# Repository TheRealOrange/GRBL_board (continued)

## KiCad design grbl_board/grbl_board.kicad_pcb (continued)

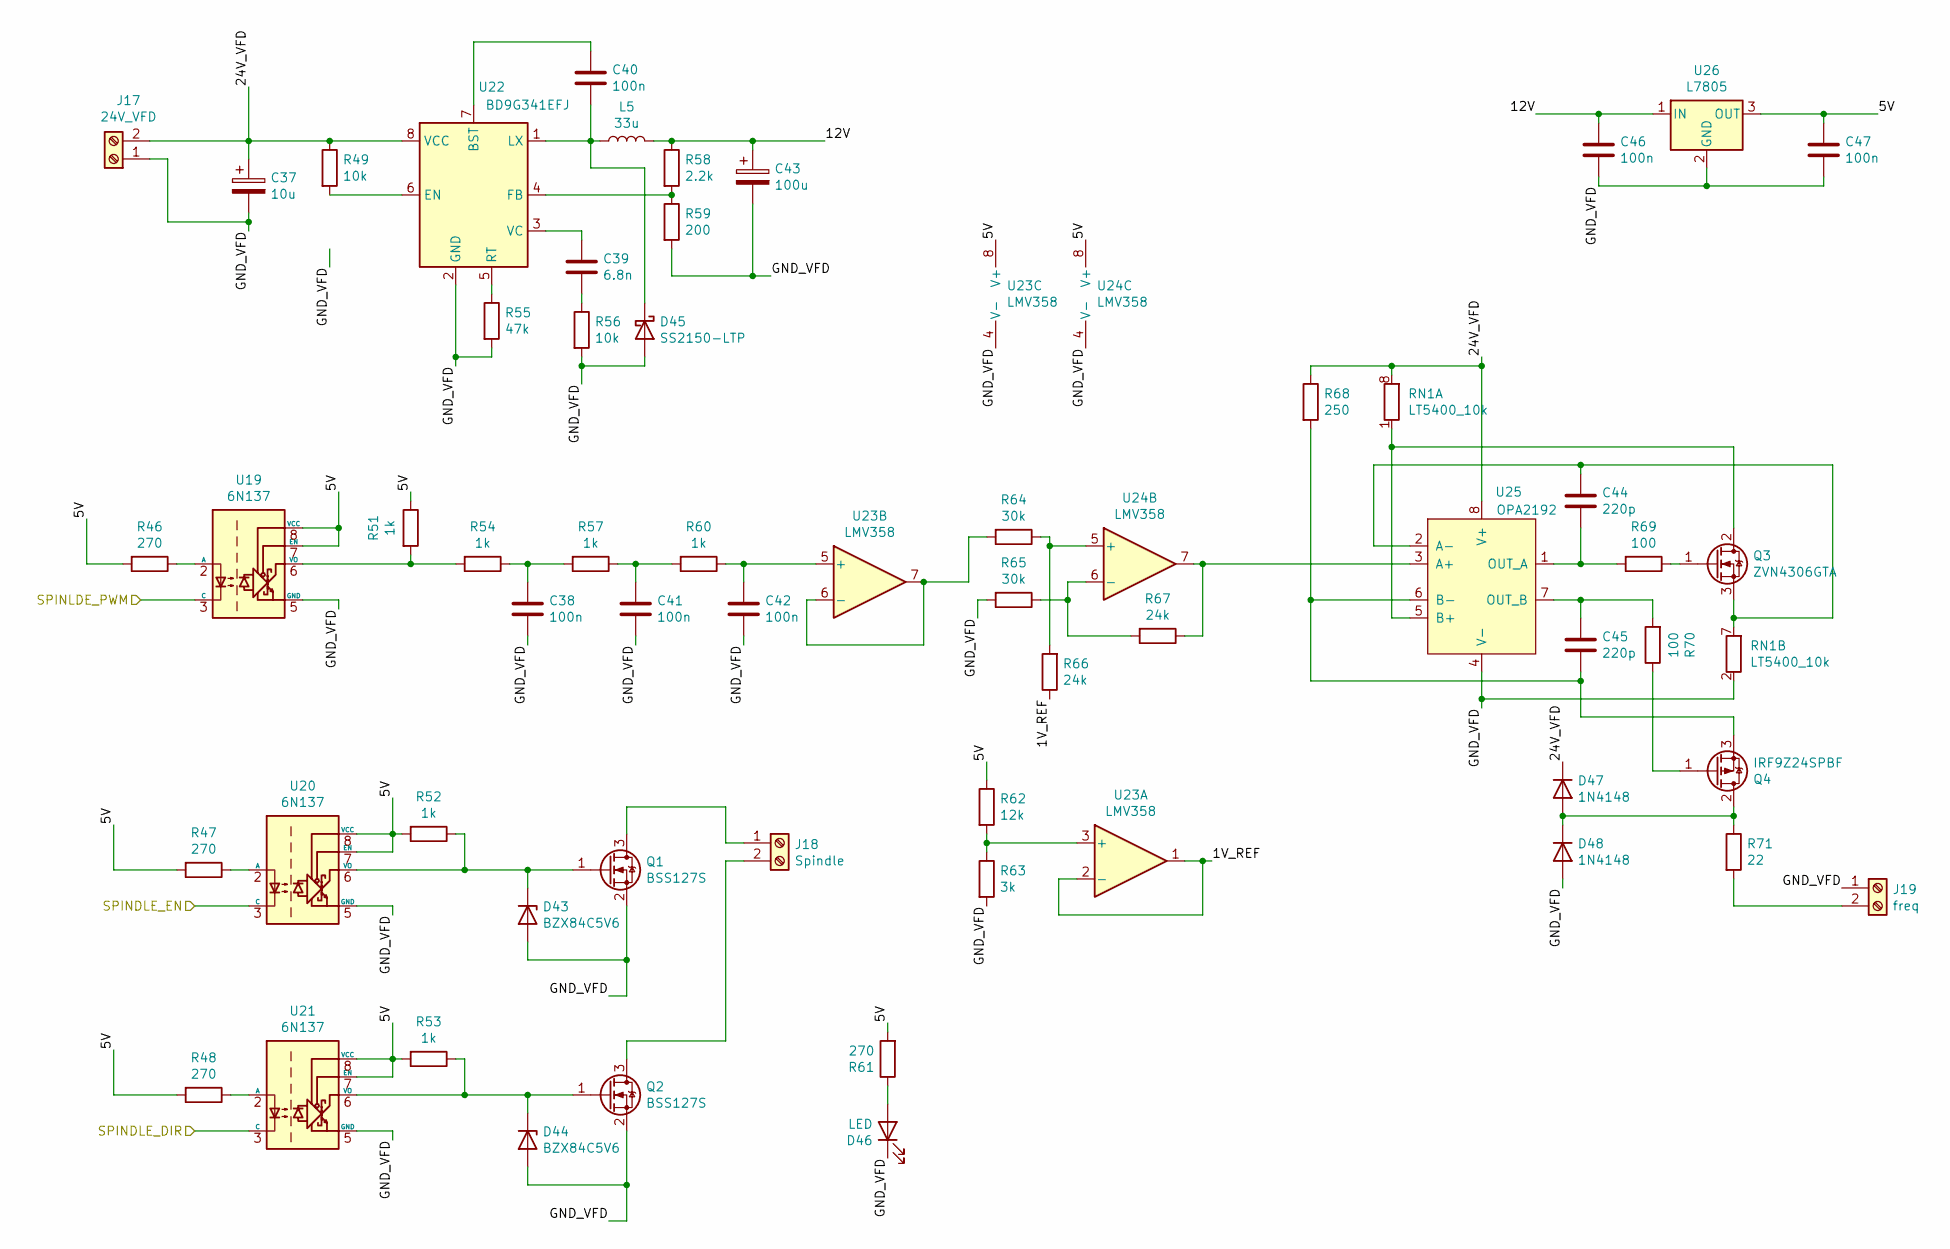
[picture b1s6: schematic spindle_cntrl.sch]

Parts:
C37: 10u; CP_Radial_D8.0mm_P3.50mm; Digikey Part No. 495-75596-ND
C38, C40, C41, C42, C46, C47: 100n; C_0603_1608Metric_Pad1.05x0.95mm_HandSolder; Digikey Part No. 1276-1941-1-ND
C39: 6.8n; C_0402_1005Metric_Pad0.74x0.62mm_HandSolder; Digikey Part No. 1276-CL05B682KB5VPNCCT-ND
C43: 100u; CP_Radial_D8.0mm_P3.50mm; Digikey Part No. 399-6119-ND
C44, C45: 220p; C_0402_1005Metric_Pad0.74x0.62mm_HandSolder; Digikey Part No. 1276-1059-1-ND
D43, D44: BZX84C5V6; D_SOT-23_ANK; Digikey Part No. 1514-BZX84C5V6TRPBFREECT-ND
D45: SS2150-LTP; D_SMA_Handsoldering; Digikey Part No. SS2150-LTPMSCT-ND
D46: LED; LED_1206_3216Metric_Pad1.42x1.75mm_HandSolder; Digikey Part No. 404-1046-1-ND
D47, D48: 1N4148; D_DO-35_SOD27_P7.62mm_Horizontal; Digikey Part No. 1N4148FS-ND
J17: 24V_VFD; PhoenixContact_MC_1,5_2-G-3.81_1x02_P3.81mm_Horizontal; Digikey Part No. ED2808-ND
J18: Spindle; PhoenixContact_MC_1,5_2-G-3.81_1x02_P3.81mm_Horizontal; Digikey Part No. ED2808-ND
J19: freq; PhoenixContact_MC_1,5_2-G-3.81_1x02_P3.81mm_Horizontal; Digikey Part No. ED2808-ND
L5: 33u; L_Vishay_IHLP-4040; Digikey Part No. 541-2273-1-ND
Q1, Q2: BSS127S; SOT-23; Digikey Part No. BSS127S-7DICT-ND
Q3: ZVN4306GTA; SOT-223-3_TabPin2; Digikey Part No. ZVN4306GCT-ND
Q4: IRF9Z24SPBF; TO-263-3_TabPin2; Digikey Part No. IRF9Z24SPBF-ND
R46, R47, R48, R61: 270; R_0805_2012Metric_Pad1.15x1.40mm_HandSolder; Digikey Part No. YAG6172CT-ND
R49, R56: 10k; R_0805_2012Metric_Pad1.15x1.40mm_HandSolder; Digikey Part No. 311-10KARCT-ND
R51, R52, R53, R54, R57, R60: 1k; R_0805_2012Metric_Pad1.15x1.40mm_HandSolder; Digikey Part No. 311-10KARCT-ND
R55: 47k; R_0805_2012Metric_Pad1.15x1.40mm_HandSolder; Digikey Part No. 311-47KARCT-ND
R58: 2.2k; R_0603_1608Metric_Pad0.98x0.95mm_HandSolder; Digikey Part No. 311-2.2KGRCT-ND
R59: 200; R_0603_1608Metric_Pad0.98x0.95mm_HandSolder; Digikey Part No. 311-200GRCT-ND
R62: 12k; R_0805_2012Metric_Pad1.15x1.40mm_HandSolder; Digikey Part No. 311-12KARCT-ND
R63: 3k; R_0603_1608Metric_Pad0.98x0.95mm_HandSolder; Digikey Part No. 311-3.0KGRCT-ND
R64, R65: 30k; R_0603_1608Metric_Pad0.98x0.95mm_HandSolder; Digikey Part No. 311-30KGRCT-ND
R66, R67: 24k; R_0805_2012Metric_Pad1.15x1.40mm_HandSolder; Digikey Part No. 311-24KARCT-ND
R68: 250; R_0603_1608Metric_Pad0.98x0.95mm_HandSolder; Digikey Part No. 13-RT0603BRE07250RLCT-ND
R69, R70: 100; R_0603_1608Metric_Pad0.98x0.95mm_HandSolder; Digikey Part No. 311-100GRCT-ND
R71: 22; R_0805_2012Metric_Pad1.15x1.40mm_HandSolder; Digikey Part No. 13-RT0805BRD0722RLCT-ND
RN1: LT5400_10k; TSSOP-8_3x3mm_P0.65mm; Digikey Part No. 505-LT5400ACMS8E-1#PBF-ND
U19, U20, U21: 6N137; DIP-8_W7.62mm_Socket; Digikey Part No. 6N137IS-ND
U22: BD9G341EFJ; HTSOP-8-1EP_3.9x4.9mm_P1.27mm_EP2.4x3.2mm_ThermalVias; Digikey Part No. BD9G341AEFJ-E2CT-ND
U23, U24: LMV358; SOIC-8_3.9x4.9mm_P1.27mm; Digikey Part No. LMV358DR2GOSCT-ND
U25: OPA2192; TSSOP-8_3x3mm_P0.65mm; Digikey Part No. 296-50480-1-ND
U26: L7805; TO-263-2; Digikey Part No. 497-1170-1-ND

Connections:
/grbl_controller/SPINDLE_DIR: U21.3 (C); also elsewhere on the board
/grbl_controller/SPINDLE_EN: U20.3 (C); also elsewhere on the board
/grbl_controller/SPINDLE_PWM: U19.3 (C); also elsewhere on the board
/spindle_cntrl/1V_REF: R66.1, U23.1, U23.2 (-)
/spindle_cntrl/5V: C47.1, R46.2, R47.2, R48.2, R51.1, R52.2, R53.2, R61.2, R62.1, U19.7 (EN), U19.8 (VCC), U20.7 (EN), U20.8 (VCC), U21.7 (EN), U21.8 (VCC), U23.8 (V+), U24.8 (V+), U26.3 (OUT)
/spindle_cntrl/12V: C43.1, C46.1, L5.2, R58.1, U26.1 (IN)
/spindle_cntrl/24V_VFD: C37.1, D47.1 (K), J17.2, R49.1, R68.1, RN1.8 (R1.2), U22.8 (VCC), U25.8 (V+)
/spindle_cntrl/GND_VFD: C37.2, C38.2, C41.2, C42.2, C43.2, C46.2, C47.2, D43.2 (A), D44.2 (A), D45.2 (A), D46.1 (K), D48.2 (A), J17.1, J19.1, Q1.2 (S), Q2.2 (S), R55.2, R56.2, R59.2, R63.2, R65.2, RN1.2 (R2.1), U19.5 (GND), U20.5 (GND), U21.5 (GND), U22.2 (GND), U23.4 (V-), U24.4 (V-), U25.4 (V-), U26.2 (GND)
unnamed: C38.1, R54.1, R57.2
unnamed: C39.1, U22.3 (VC)
unnamed: C39.2, R56.1
unnamed: C40.1, U22.7 (BST)
unnamed: C40.2, D45.1 (K), L5.1, U22.1 (LX)
unnamed: C41.1, R57.1, R60.2
unnamed: C42.1, R60.1, U23.5 (+)
unnamed: C44.1, Q3.3 (S), RN1.7 (R2.2), U25.2 (A-)
unnamed: C44.2, R69.2, U25.1 (OUT_A)
unnamed: C45.1, R70.2, U25.7 (OUT_B)
unnamed: C45.2, Q4.3 (S), R68.2, U25.6 (B-)
unnamed: D43.1 (K), Q1.1 (G), R52.1, U20.6 (VO)
unnamed: D44.1 (K), Q2.1 (G), R53.1, U21.6 (VO)
unnamed: D46.2 (A), R61.1
unnamed: D47.2 (A), D48.1 (K), Q4.2 (D), R71.1
unnamed: J18.1, Q1.3 (D)
unnamed: J18.2, Q2.3 (D)
unnamed: J19.2, R71.2
unnamed: Q3.1 (G), R69.1
unnamed: Q3.2 (D), RN1.1 (R1.1), U25.5 (B+)
unnamed: Q4.1 (G), R70.1
unnamed: R46.1, U19.2 (A)
unnamed: R47.1, U20.2 (A)
unnamed: R48.1, U21.2 (A)
unnamed: R49.2, U22.6 (EN)
unnamed: R51.2, R54.2, U19.6 (VO)
unnamed: R55.1, U22.5 (RT)
unnamed: R58.2, R59.1, U22.4 (FB)
unnamed: R62.2, R63.1, U23.3 (+)
unnamed: R64.1, R66.2, U24.5 (+)
unnamed: R64.2, U23.6 (-), U23.7
unnamed: R65.1, R67.2, U24.6 (-)
unnamed: R67.1, U24.7, U25.3 (A+)

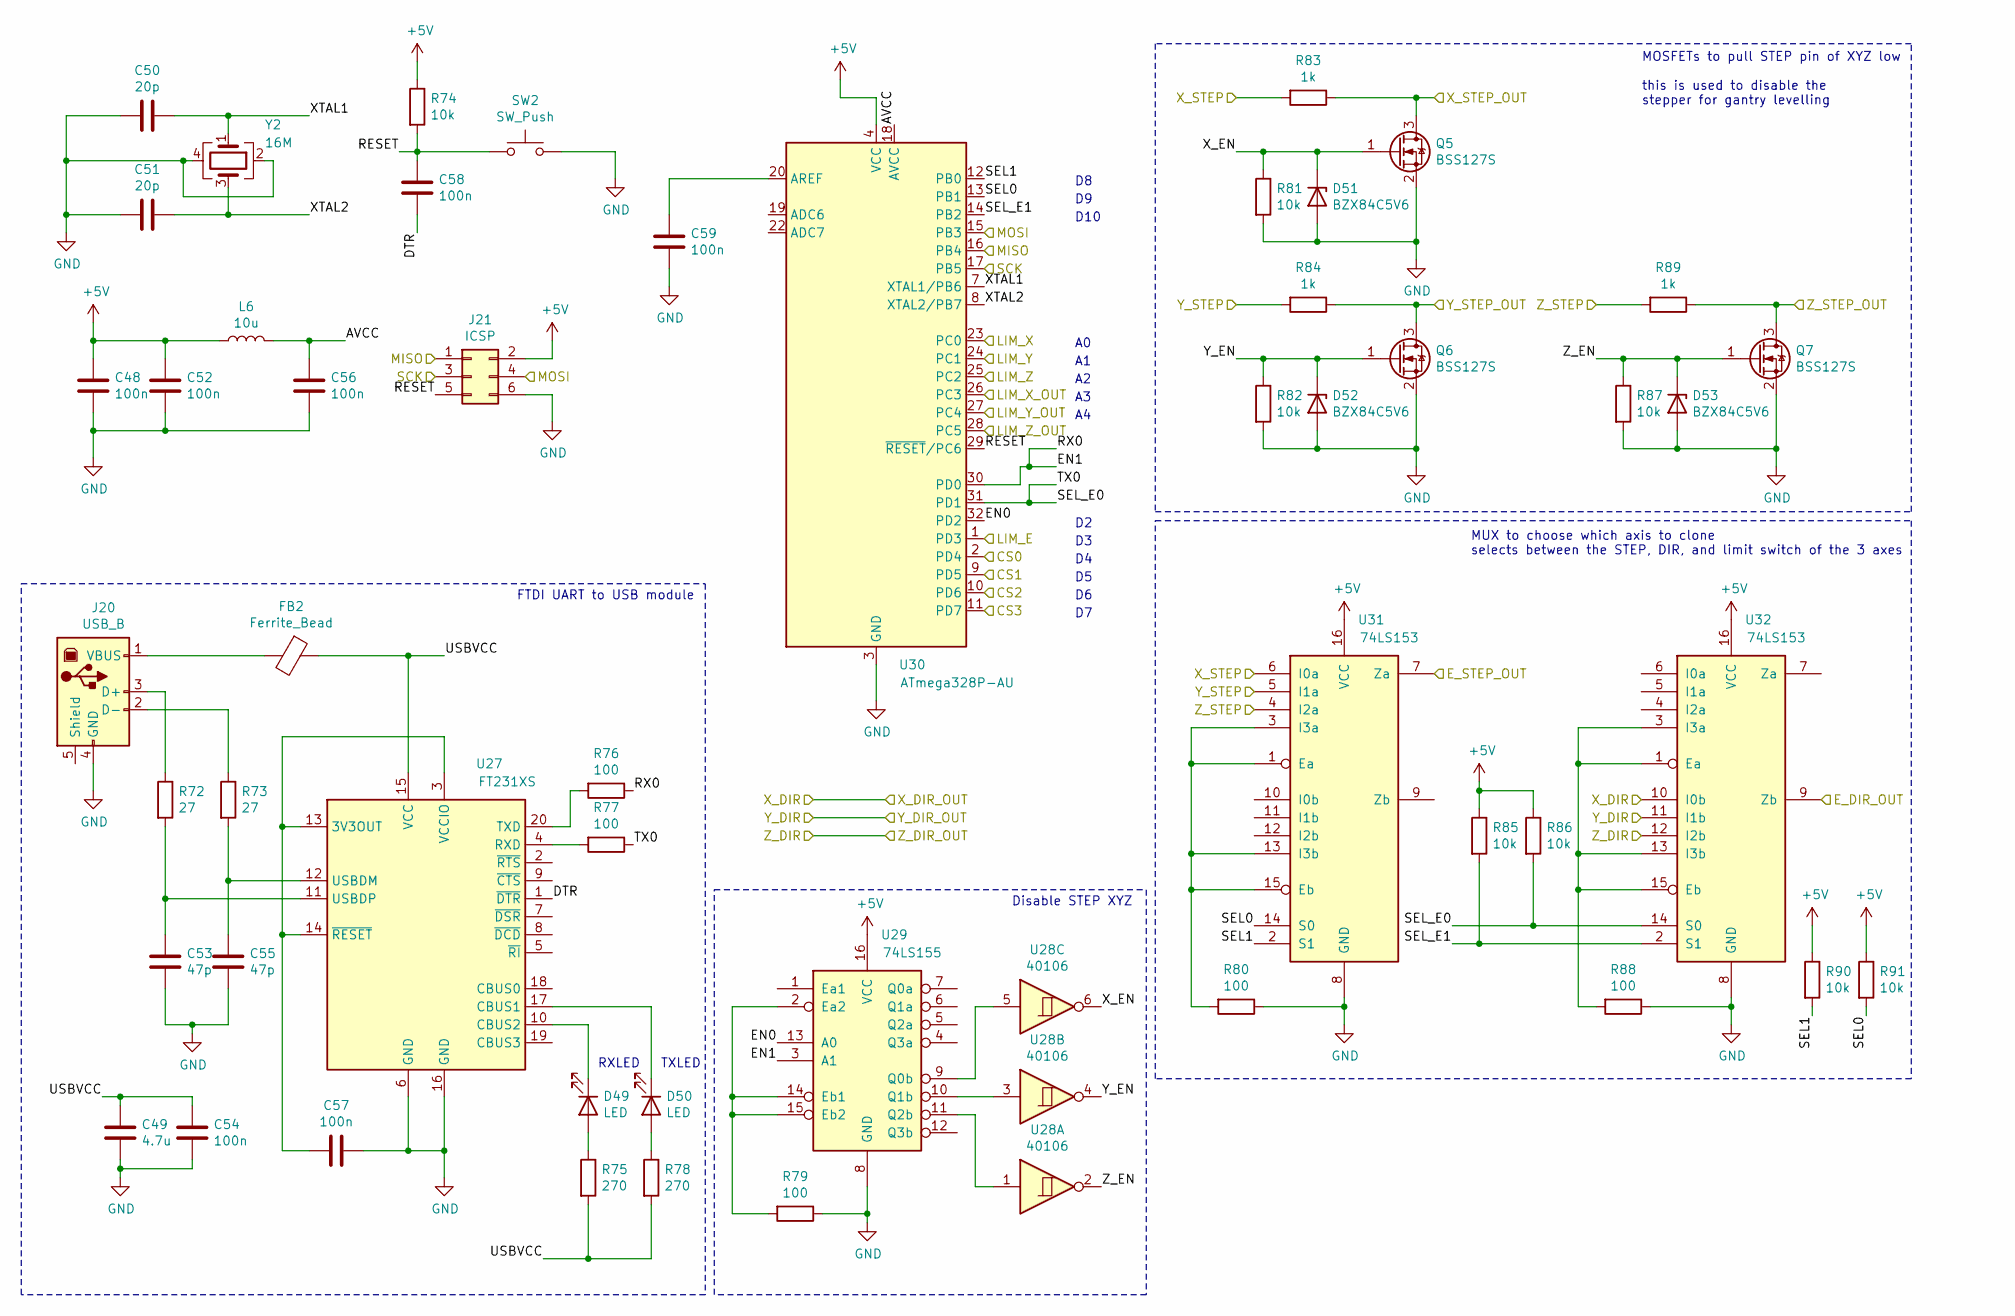
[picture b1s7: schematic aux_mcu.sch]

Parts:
C48, C52, C54, C56, C57, C58, C59: 100n; C_0603_1608Metric_Pad1.05x0.95mm_HandSolder; Digikey Part No. 1276-1941-1-ND
C49: 4.7u; C_1206_3216Metric_Pad1.33x1.80mm_HandSolder; Digikey Part No. 1276-6781-1-ND
C50, C51: 20p; C_0603_1608Metric_Pad1.05x0.95mm_HandSolder; Digikey Part No. 1276-1187-1-ND
C53, C55: 47p; C_0402_1005Metric_Pad0.74x0.62mm_HandSolder; Digikey Part No. 1276-1699-1-ND
D49, D50: LED; LED_1206_3216Metric_Pad1.42x1.75mm_HandSolder; Digikey Part No. 404-1042-1-ND
D51, D52, D53: BZX84C5V6; D_SOT-23_ANK; Digikey Part No. 1514-BZX84C5V6TRPBFREECT-ND
FB2: Ferrite_Bead; C_0603_1608Metric_Pad1.05x0.95mm_HandSolder; Digikey Part No. 732-1591-1-ND
J20: USB_B; USB_B_OST_USB-B1HSxx_Horizontal; Digikey Part No. 380-1492-ND
J21: ICSP; PinHeader_2x03_P2.54mm_Vertical; Digikey Part No. 609-3234-ND
L6: 10u; L_0805_2012Metric_Pad1.05x1.20mm_HandSolder; Digikey Part No. 490-4029-1-ND
Q5, Q6, Q7: BSS127S; SOT-23; Digikey Part No. BSS127S-7DICT-ND
R72, R73: 27; R_0603_1608Metric_Pad0.98x0.95mm_HandSolder; Digikey Part No. 311-27GRCT-ND
R74, R81, R82, R85, R86, R87, R90, R91: 10k; R_0805_2012Metric_Pad1.15x1.40mm_HandSolder; Digikey Part No. 311-10KARCT-ND
R75, R78: 270; R_0805_2012Metric_Pad1.15x1.40mm_HandSolder; Digikey Part No. YAG6172CT-ND
R76, R77, R79, R80, R88: 100; R_0603_1608Metric_Pad0.98x0.95mm_HandSolder; Digikey Part No. 311-100GRCT-ND
R83, R84, R89: 1k; R_1206_3216Metric_Pad1.30x1.75mm_HandSolder; Digikey Part No. 311-1.0KERCT-ND
SW2: SW_Push; SW_Push_1P1T_NO_6x6mm_H9.5mm; Digikey Part No. EG2526CT-ND
U27: FT231XS; SSOP-20_3.9x8.7mm_P0.635mm; Digikey Part No. 768-1129-1-ND
U28: 40106; TSSOP-14_4.4x5mm_P0.65mm; Digikey Part No. HEF40106BTT,112-ND
U29: 74LS155; SOIC-16_3.9x9.9mm_P1.27mm; Digikey Part No. 296-33960-5-ND
U30: ATmega328P-AU; TQFP-32_7x7mm_P0.8mm; Digikey Part No. ATMEGA328P-AU-ND
U31, U32: 74LS153; SOIC-16_3.9x9.9mm_P1.27mm; Digikey Part No. 296-3653-5-ND
Y2: 16M; Crystal_SMD_SeikoEpson_TSX3225-4Pin_3.2x2.5mm_HandSoldering; Digikey Part No. SER4372CT-ND

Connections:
+5V: C48.1, C52.1, J21.2, L6.1, R74.1, R85.1, R86.1, R90.1, R91.1, U29.16 (VCC), U30.4 (VCC), U30.6 (VCC), U31.16 (VCC), U32.16 (VCC); also elsewhere on the board
/CS_E: U30.11 (PD7); also elsewhere on the board
/CS_X: U30.2 (PD4); also elsewhere on the board
/CS_Y: U30.9 (PD5); also elsewhere on the board
/CS_Z: U30.10 (PD6); also elsewhere on the board
/MISO: J21.1, U30.16 (PB4); also elsewhere on the board
/MOSI: J21.4, U30.15 (PB3); also elsewhere on the board
/SCK: J21.3, U30.17 (PB5); also elsewhere on the board
/aux_mcu/AVCC: C56.1, L6.2, U30.18 (AVCC)
/aux_mcu/DTR: C58.2, U27.1 (~DTR)
/aux_mcu/EN0: U29.13 (A0), U30.32 (PD2)
/aux_mcu/EN1: R76.1, U29.3 (A1), U30.30 (PD0)
/aux_mcu/LIM_E: U30.1 (PD3); also elsewhere on the board
/aux_mcu/LIM_X: U30.23 (PC0); also elsewhere on the board
/aux_mcu/LIM_Y: U30.24 (PC1); also elsewhere on the board
/aux_mcu/LIM_Z: U30.25 (PC2); also elsewhere on the board
/aux_mcu/RESET: C58.1, J21.5, R74.2, SW2.1, U30.29 (~RESET~/PC6)
/aux_mcu/SEL0: R91.2, U30.13 (PB1), U31.14 (S0)
/aux_mcu/SEL1: R90.2, U30.12 (PB0), U31.2 (S1)
/aux_mcu/SEL_E0: R77.1, R86.2, U30.31 (PD1), U32.14 (S0)
/aux_mcu/SEL_E1: R85.2, U30.14 (PB2), U32.2 (S1)
/aux_mcu/USBVCC: C49.1, C54.1, FB2.1, R75.2, R78.2, U27.15 (VCC)
/aux_mcu/XTAL1: C50.1, U30.7 (XTAL1/PB6), Y2.1
/aux_mcu/XTAL2: C51.1, U30.8 (XTAL2/PB7), Y2.3
/aux_mcu/X_EN: D51.1 (K), Q5.1 (G), R81.1, U28.6
/aux_mcu/Y_EN: D52.1 (K), Q6.1 (G), R82.1, U28.4
/aux_mcu/Z_EN: D53.1 (K), Q7.1 (G), R87.1, U28.2
/grbl_controller/DIR_X: U32.10 (I0b); also elsewhere on the board
/grbl_controller/DIR_Y: U32.11 (I1b); also elsewhere on the board
/grbl_controller/DIR_Z: U32.12 (I2b); also elsewhere on the board
/grbl_controller/LIM_X: U30.26 (PC3); also elsewhere on the board
/grbl_controller/LIM_Y: U30.27 (PC4); also elsewhere on the board
/grbl_controller/LIM_Z: U30.28 (PC5); also elsewhere on the board
/grbl_controller/STEP_X: R83.2, U31.6 (I0a); also elsewhere on the board
/grbl_controller/STEP_Y: R84.2, U31.5 (I1a); also elsewhere on the board
/grbl_controller/STEP_Z: R89.2, U31.4 (I2a); also elsewhere on the board
/stepper_drivers/E_DIR: U32.9 (Zb); also elsewhere on the board
/stepper_drivers/E_STEP: U31.7 (Za); also elsewhere on the board
/stepper_drivers/X_STEP: Q5.3 (D), R83.1; also elsewhere on the board
/stepper_drivers/Y_STEP: Q6.3 (D), R84.1; also elsewhere on the board
/stepper_drivers/Z_STEP: Q7.3 (D), R89.1; also elsewhere on the board
GND: C48.2, C49.2, C50.2, C51.2, C52.2, C53.2, C54.2, C55.2, C56.2, C57.1, C59.2, D51.2 (A), D52.2 (A), D53.2 (A), J20.4 (GND), J21.6, Q5.2 (S), Q6.2 (S), Q7.2 (S), R79.1, R80.1, R81.2, R82.2, R87.2, R88.1, SW2.2, U27.6 (GND), U27.16 (GND), U29.8 (GND), U30.3 (GND), U30.5 (GND), U30.21 (GND), U31.8 (GND), U32.8 (GND), Y2.2, Y2.4; also elsewhere on the board
unnamed: C53.1, R72.2, U27.11 (USBDP)
unnamed: C55.1, R73.2, U27.12 (USBDM)
unnamed: C57.2, U27.3 (VCCIO), U27.13 (3V3OUT), U27.14 (~RESET)
unnamed: C59.1, U30.20 (AREF)
unnamed: D49.1 (K), U27.10 (CBUS2)
unnamed: D49.2 (A), R75.1
unnamed: D50.1 (K), U27.17 (CBUS1)
unnamed: D50.2 (A), R78.1
unnamed: FB2.2, J20.1 (VBUS)
unnamed: J20.2 (D-), R73.1
unnamed: J20.3 (D+), R72.1
unnamed: R76.2, U27.20 (TXD)
unnamed: R77.2, U27.4 (RXD)
unnamed: R79.2, U29.2 (Ea2), U29.14 (Eb1), U29.15 (Eb2)
unnamed: R80.2, U31.1 (Ea), U31.3 (I3a), U31.13 (I3b), U31.15 (Eb)
unnamed: R88.2, U32.1 (Ea), U32.3 (I3a), U32.13 (I3b), U32.15 (Eb)
unnamed: U28.1, U29.11 (Q2b)
unnamed: U28.3, U29.10 (Q1b)
unnamed: U28.5, U29.9 (Q0b)

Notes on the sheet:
D10
TXLED
RXLED
FTDI UART to USB module
Disable STEP XYZ
MOSFETs to pull STEP pin of XYZ low this is used to disable the stepper for gantry levelling
MUX to choose which axis to clone selects between the STEP, DIR, and limit switch of the 3 axes

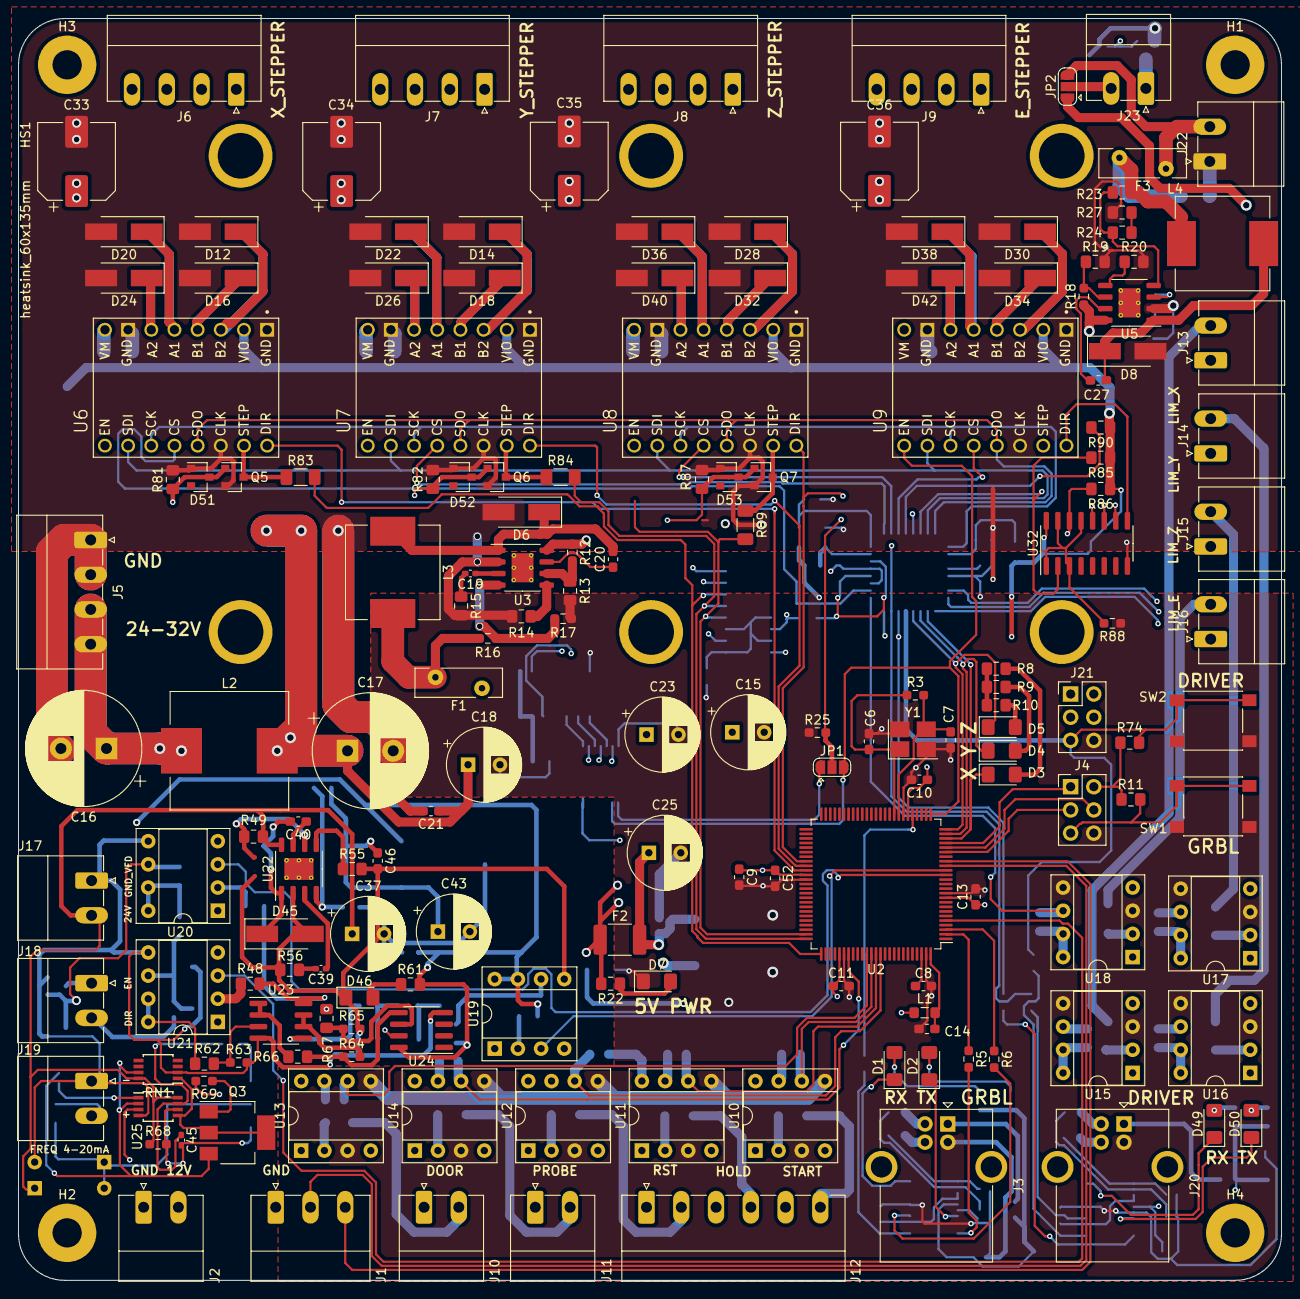
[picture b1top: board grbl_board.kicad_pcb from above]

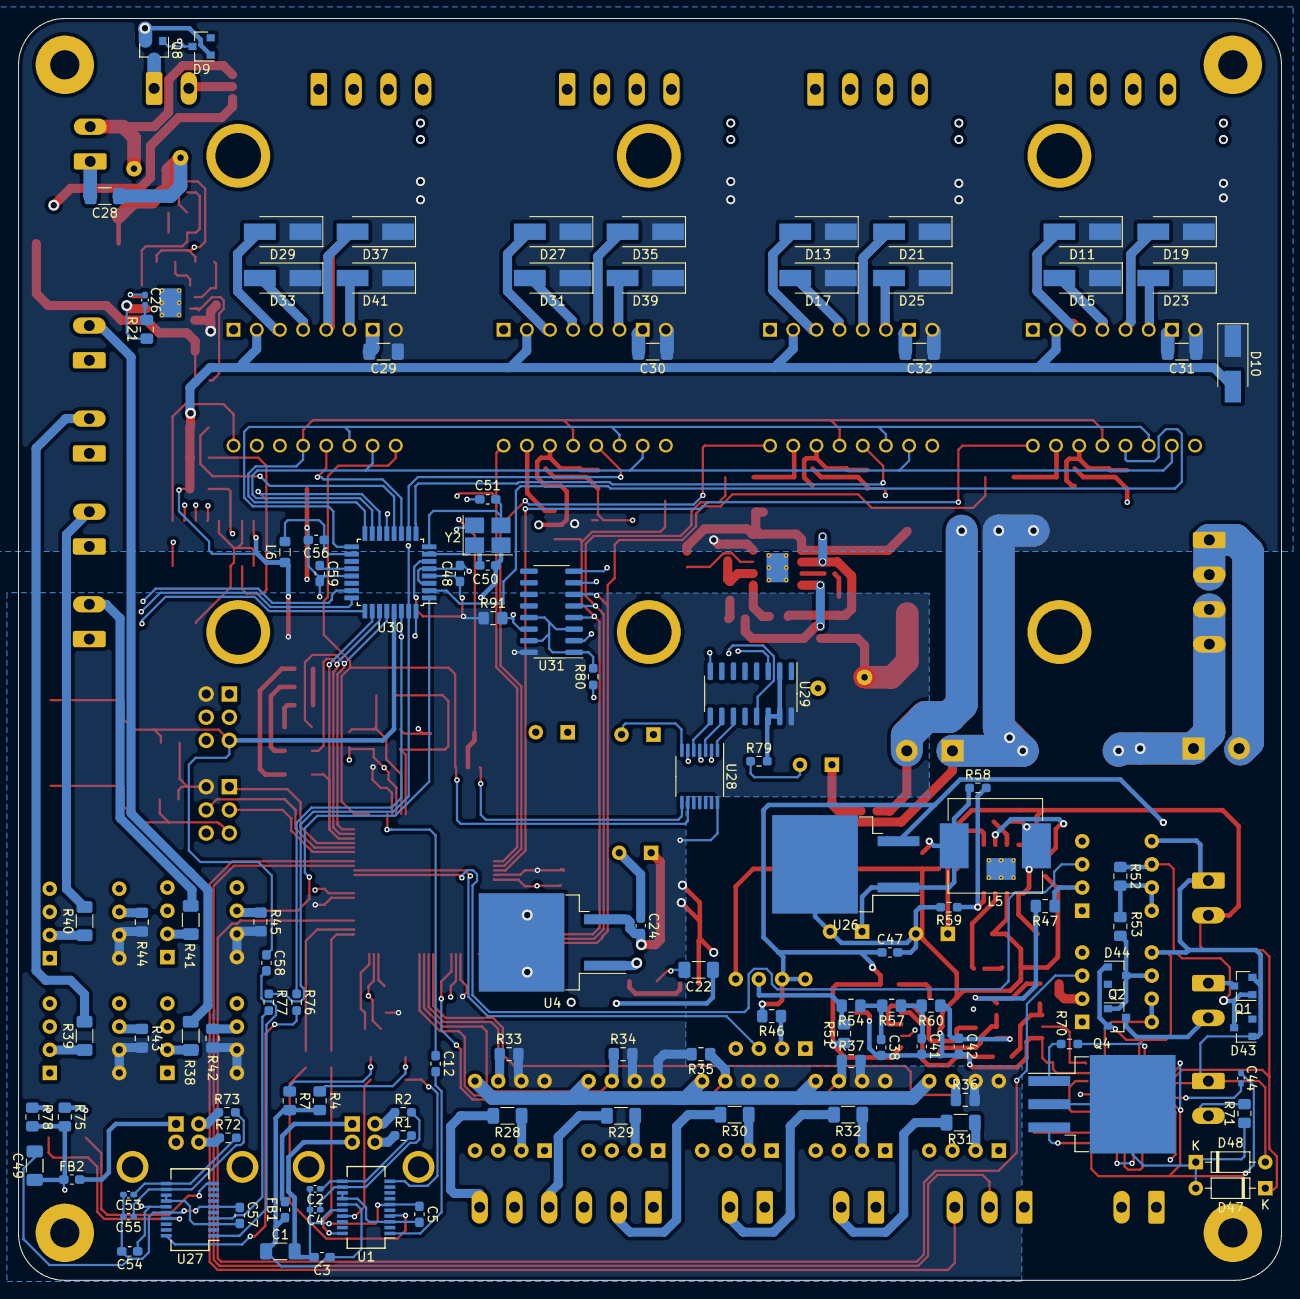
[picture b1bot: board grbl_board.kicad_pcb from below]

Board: 4 copper layers, 138.4 x 138.3 mm, 287 parts (113 on the bottom side), 199 nets.

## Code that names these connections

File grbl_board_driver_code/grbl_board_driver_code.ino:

#include <TMCStepper.h>

//#define TMCSTEPPER

#define CLONED_AXIS           1  //0:x, 1:y, 2:z
#define LIMIT_INVERT       false

// stepper motor config
#define MICROSTEPS            0
#define CURRENT_MA         2500
#define HOLD_MULTIPLIER     0.8
#define INTERPOLATE        true

#define STEALTHCHOP       false

// experimental
//#define SQUARE_WAVE_STEPPING

#define CHOPPER_TIMING {4, -2, 1}

#define LIM_X_IN     A0
#define LIM_Y_IN     A1
#define LIM_Z_IN     A2

#define LIM_X_OUT    A3
#define LIM_Y_OUT    A4
#define LIM_Z_OUT    A5

#define LIM_E        3

#define EN0 2
#define EN1 0

#define SEL0 9
#define SEL1 8

#define SEL_E0 1
#define SEL_E1 10

#define CS_X 4
#define CS_Y 5
#define CS_Z 6
#define CS_E 7

uint8_t lim_e_val = 0, lim_cloned_val = 0;
boolean pulloff = false;
long levelling = -1;

#define R_SENSE 0.075f // Match to your driver
                      // SilentStepStick series use 0.11
                      // UltiMachine Einsy and Archim2 boards use 0.2
                      // Panucatt BSD2660 uses 0.1
                      // Watterott TMC5160 uses 0.075

typedef struct {
  uint8_t toff;    // [1..15]
  int8_t hend;     // [-3..12]
  uint8_t hstrt;   // [1..8]
} chopper_timing_t;

#ifdef TMCSTEPPER
  TMC5160Stepper x_stepper(CS_X, R_SENSE);
  TMC5160Stepper y_stepper(CS_Y, R_SENSE);
  TMC5160Stepper z_stepper(CS_Z, R_SENSE);
  TMC5160Stepper e_stepper(CS_E, R_SENSE);
  
  TMC5160Stepper steppers[] = {x_stepper, y_stepper, z_stepper, e_stepper};
  int8_t timings[] = CHOPPER_TIMING; // Default 4, -2, 1
  static constexpr chopper_timing_t chop_init = CHOPPER_TIMING;
#endif
int8_t enable = LOW , disable = HIGH;


void stopStepper(int num) {
  digitalWrite(EN0, num&0x1);
  digitalWrite(EN1, (num&0x2) >> 1);
}

void selectStepClone(int num) {
  digitalWrite(SEL0, num&0x1);
  digitalWrite(SEL1, (num&0x2) >> 1);
}

void selectAxisClone(int num) {
  digitalWrite(SEL_E0, num&0x1);
  digitalWrite(SEL_E1, (num&0x2) >> 1);
}

void setup() {
  pinMode(SEL0, OUTPUT);
  pinMode(SEL1, OUTPUT);
  pinMode(SEL_E0, OUTPUT);
  pinMode(SEL_E1, OUTPUT);
  pinMode(EN0, OUTPUT);
  pinMode(EN1, OUTPUT);
  
  pinMode(LIM_X_OUT, OUTPUT);
  pinMode(LIM_Y_OUT, OUTPUT);
  pinMode(LIM_Z_OUT, OUTPUT);

  pinMode(LIM_X_IN, INPUT_PULLUP);
  pinMode(LIM_Y_IN, INPUT_PULLUP);
  pinMode(LIM_Z_IN, INPUT_PULLUP);

  pinMode(LIM_E, INPUT_PULLUP);

  pinMode(CS_X, OUTPUT);
  pinMode(CS_Y, OUTPUT);
  pinMode(CS_Z, OUTPUT);
  pinMode(CS_E, OUTPUT);

  if (LIMIT_INVERT) {
    enable = HIGH;
    disable = LOW;
  }

  #ifdef TMCSTEPPER
    SPI.begin();
    
    for (auto& st: steppers){
      st.begin();                 //  SPI: Init CS pins and possible SW SPI pins
      st.reset();
      st.toff(0);
      st.push();
      st.toff(chop_init.toff);
      
      CHOPCONF_t chopconf{0};
      chopconf.tbl = 0b01;
      chopconf.toff = chop_init.toff;
      chopconf.intpol = INTERPOLATE;
      chopconf.hend = chop_init.hend + 3;
      chopconf.hstrt = chop_init.hstrt - 1;
      #ifdef SQUARE_WAVE_STEPPING
        chopconf.dedge = true;
      #endif
      st.CHOPCONF(chopconf.sr);
      
      st.rms_current(CURRENT_MA, HOLD_MULTIPLIER);
      st.microsteps(MICROSTEPS);
      st.iholddelay(10);
      st.TPOWERDOWN(128); // ~2s until driver lowers to hold current
      
      st.en_pwm_mode(STEALTHCHOP); // Toggle stealthChop on TMC2130/2160/5130/5160
      st.TPWMTHRS(500);   
      st.TCOOLTHRS(0xFFFFF); // 20bit max - Lower velocity threshold for switching on CoolStep and stop on stall. Below this velocity CoolStep becomes disabled (not used in STEP/DIR mode). Adapt to the lower limit of the velocity range where StallGuard2 gives a stable result.
      st.THIGH(0);    // Upper velocity threshold value for CoolStep and stop on stall. Above this velocity CoolStep becomes disabled. Adapt to the velocity range where StallGuard2 gives a stable result.
      st.semin(5);    // [0-15] If the StallGuard2 result falls below SEMIN*32, the motor current becomes increased to reduce motor load angle. 0 = smart current control CoolStep off
      st.semax(2);    // [0-15] If the StallGuard2 result is equal to or above (SEMIN+SEMAX+1)*32, the motor current becomes decreased to save energy.
      st.sedn(0b01);  // For each 8 StallGuard2 values decrease by one
     
      TMC2160_n::PWMCONF_t pwmconf{0};
      pwmconf.pwm_lim = 12;
      pwmconf.pwm_reg = 8;
      pwmconf.pwm_autograd = true;
      pwmconf.pwm_autoscale = true;
      pwmconf.pwm_freq = 0b01;
      pwmconf.pwm_grad = 14;
      pwmconf.pwm_ofs = 36;
      st.PWMCONF(pwmconf.sr);
      st.drvstrength(0b11);   // 00: weak  01: weak+TC (medium above OTPW level)  10: medium  11: strong  
  
      st.sfilt(true);
      
      st.GSTAT(); // Clear GSTAT
      st.RAMP_STAT();
  
    }
  #else
    pinMode(11, OUTPUT);
    pinMode(12, OUTPUT);
    pinMode(13, OUTPUT);
  
    digitalWrite(11, LOW);
    digitalWrite(12, HIGH);
    digitalWrite(13, LOW);
    
    digitalWrite(CS_X, LOW);
    digitalWrite(CS_Y, LOW);
    digitalWrite(CS_Z, LOW);
    digitalWrite(CS_E, LOW);
  #endif
  
  stopStepper(3);
  selectStepClone(CLONED_AXIS);
  selectAxisClone(CLONED_AXIS);
}

void loop() {
  switch(CLONED_AXIS) {
    case 0: 
    digitalWrite(LIM_Y_OUT, digitalRead(LIM_Y_IN));
    digitalWrite(LIM_Z_OUT, digitalRead(LIM_Z_IN));
    lim_cloned_val = digitalRead(LIM_X_IN);
    break;
    case 1: 
    digitalWrite(LIM_X_OUT, digitalRead(LIM_X_IN));
    digitalWrite(LIM_Z_OUT, digitalRead(LIM_Z_IN));
    lim_cloned_val = digitalRead(LIM_Y_IN);
    break;
    case 2: 
    digitalWrite(LIM_X_OUT, digitalRead(LIM_X_IN));
    digitalWrite(LIM_Y_OUT, digitalRead(LIM_Y_IN));
    lim_cloned_val = digitalRead(LIM_Z_IN);
    break;
    default: break;
  }
  
  lim_e_val = digitalRead(LIM_E);
  if (lim_e_val != lim_cloned_val && !pulloff && !(levelling >= 0 && millis()-levelling < 3000)) {
    switch(CLONED_AXIS) {
      case 0: digitalWrite(LIM_X_OUT, enable); break;
      case 1: digitalWrite(LIM_Y_OUT, enable); break;
      case 2: digitalWrite(LIM_Z_OUT, enable); break;
      default: break;
    }
    if (lim_cloned_val == disable) stopStepper(CLONED_AXIS);
    if (lim_e_val == disable) selectStepClone(3);
    if (levelling <0) levelling = millis();
  } else if (lim_e_val == lim_cloned_val) {
    stopStepper(3);
    selectStepClone(CLONED_AXIS);
    if (lim_e_val == enable) {
      pulloff = false;
      switch(CLONED_AXIS) {
        case 0: digitalWrite(LIM_X_OUT, enable); break;
        case 1: digitalWrite(LIM_Y_OUT, enable); break;
        case 2: digitalWrite(LIM_Z_OUT, enable); break;
        default: break;
      }
    } else {
      pulloff = true;
      switch(CLONED_AXIS) {
        case 0: digitalWrite(LIM_X_OUT, disable); break;
        case 1: digitalWrite(LIM_Y_OUT, disable); break;
        case 2: digitalWrite(LIM_Z_OUT, disable); break;
        default: break;
      }
    } 
  } else if (levelling >= 0 && millis()-levelling < 3000) {
    switch(CLONED_AXIS) {
      case 0: digitalWrite(LIM_X_OUT, disable); break;
      case 1: digitalWrite(LIM_Y_OUT, disable); break;
      case 2: digitalWrite(LIM_Z_OUT, disable); break;
      default: break;
    }
  }
  
}

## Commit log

2021-10-26 created project
2021-10-28 finished GRBL controller
2021-10-28 power supply stage
2021-10-28 motor driver and mcu and limit switches
2021-10-28 changed limit switch control
2021-10-28 spindle control stage (not complete)
2021-10-28 spindle control stage
2021-10-29 edited motor outputs
2021-10-30 changed to matched resistor
2021-10-30 added some footprint associations
2021-10-30 complete footprint associations
2021-10-30 fixed mismatch for 6n137
2021-10-31 routing done
2021-11-01 added connector labels and tmc 3d model
2021-11-01 added usb 3d model and fixed footprint associations
2021-11-01 added some pictures to readme
2021-11-01 minor formatting of readme
2021-11-01 tidy up
2021-11-03 added more filtering caps
2021-11-04 added some descriptions in the schematic and added gerber file
2021-11-04 fixed limit switch disconnect issue
2021-11-05 fixed copper fill
2021-11-09 added GRBL board stepper driver init and gantry level code
2021-12-12 fixed pullup resistors on board, and 5v regulator overheating, and stepper driver flipped
2021-12-12 moved connectors further out
2021-12-12 added limit switch indicator LEDs
2022-01-23 updated board with 24V reg
